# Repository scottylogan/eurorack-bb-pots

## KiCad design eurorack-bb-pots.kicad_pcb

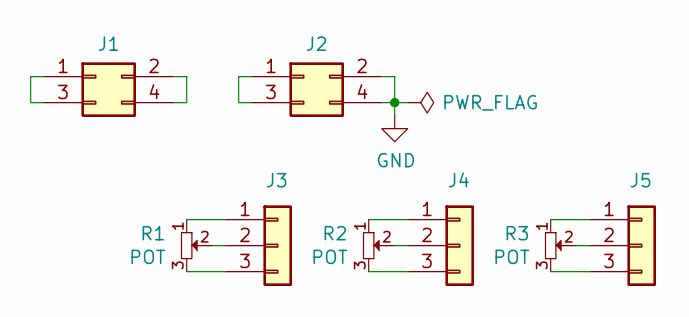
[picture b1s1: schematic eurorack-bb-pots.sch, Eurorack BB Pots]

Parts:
J1, J2: Conn_02x02_Odd_Even; PinHeader_2x02_P2.54mm_Vertical
J3, J4, J5: Conn_01x03; PinSocket_1x03_P2.54mm_Vertical
R1, R2, R3: POT; Potentiometer_Thonk_Alpha_9mm_Vertical

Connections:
GND: J2.2, J2.4
unnamed: J1.1, J1.3
unnamed: J1.2, J1.4
unnamed: J2.1, J2.3
unnamed: J3.1, R1.1
unnamed: J3.2, R1.2
unnamed: J3.3, R1.3
unnamed: J4.1, R2.1
unnamed: J4.2, R2.2
unnamed: J4.3, R2.3
unnamed: J5.1, R3.1
unnamed: J5.2, R3.2
unnamed: J5.3, R3.3

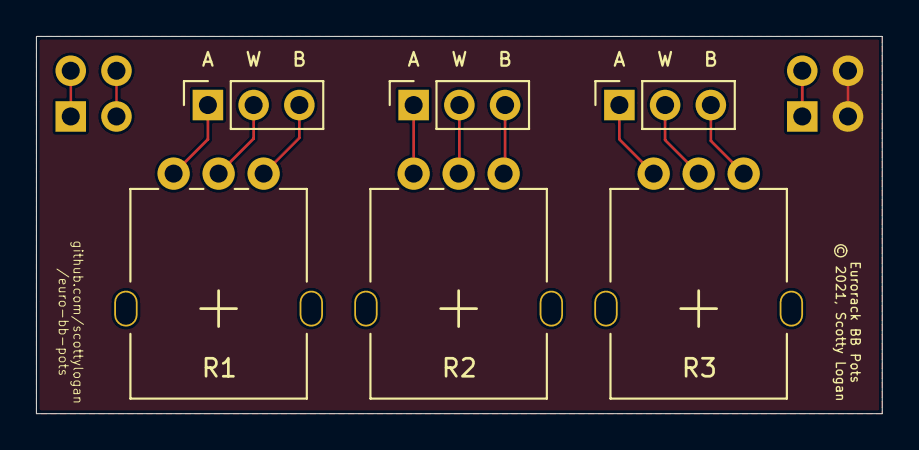
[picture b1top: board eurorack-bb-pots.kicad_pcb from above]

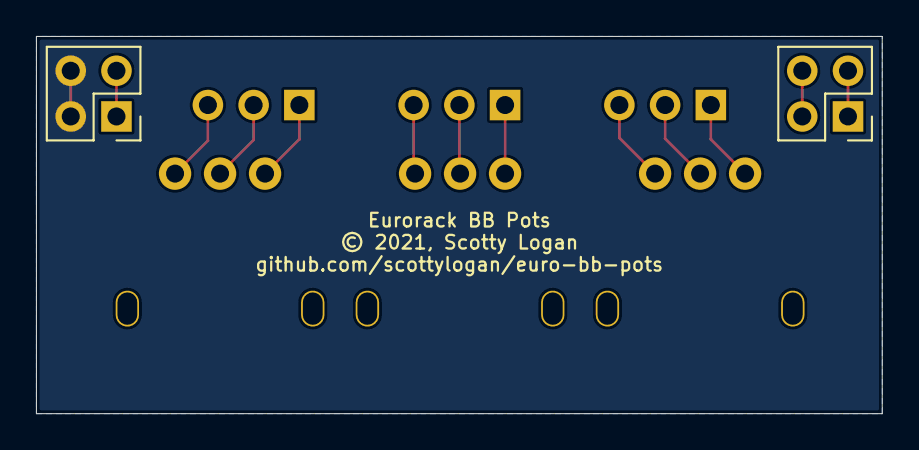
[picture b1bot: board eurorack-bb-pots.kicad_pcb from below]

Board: 2 copper layers, 47.0 x 21.0 mm, 8 parts (2 on the bottom side), 13 nets.

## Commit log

2025-04-16 added LICENSE

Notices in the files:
eurorack-bb-pots.kicad_pcb:
© 2021, Scotty Logan
